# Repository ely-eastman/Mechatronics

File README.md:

# Mechatronics
For Northwestern's Advanced Mechatronics Class

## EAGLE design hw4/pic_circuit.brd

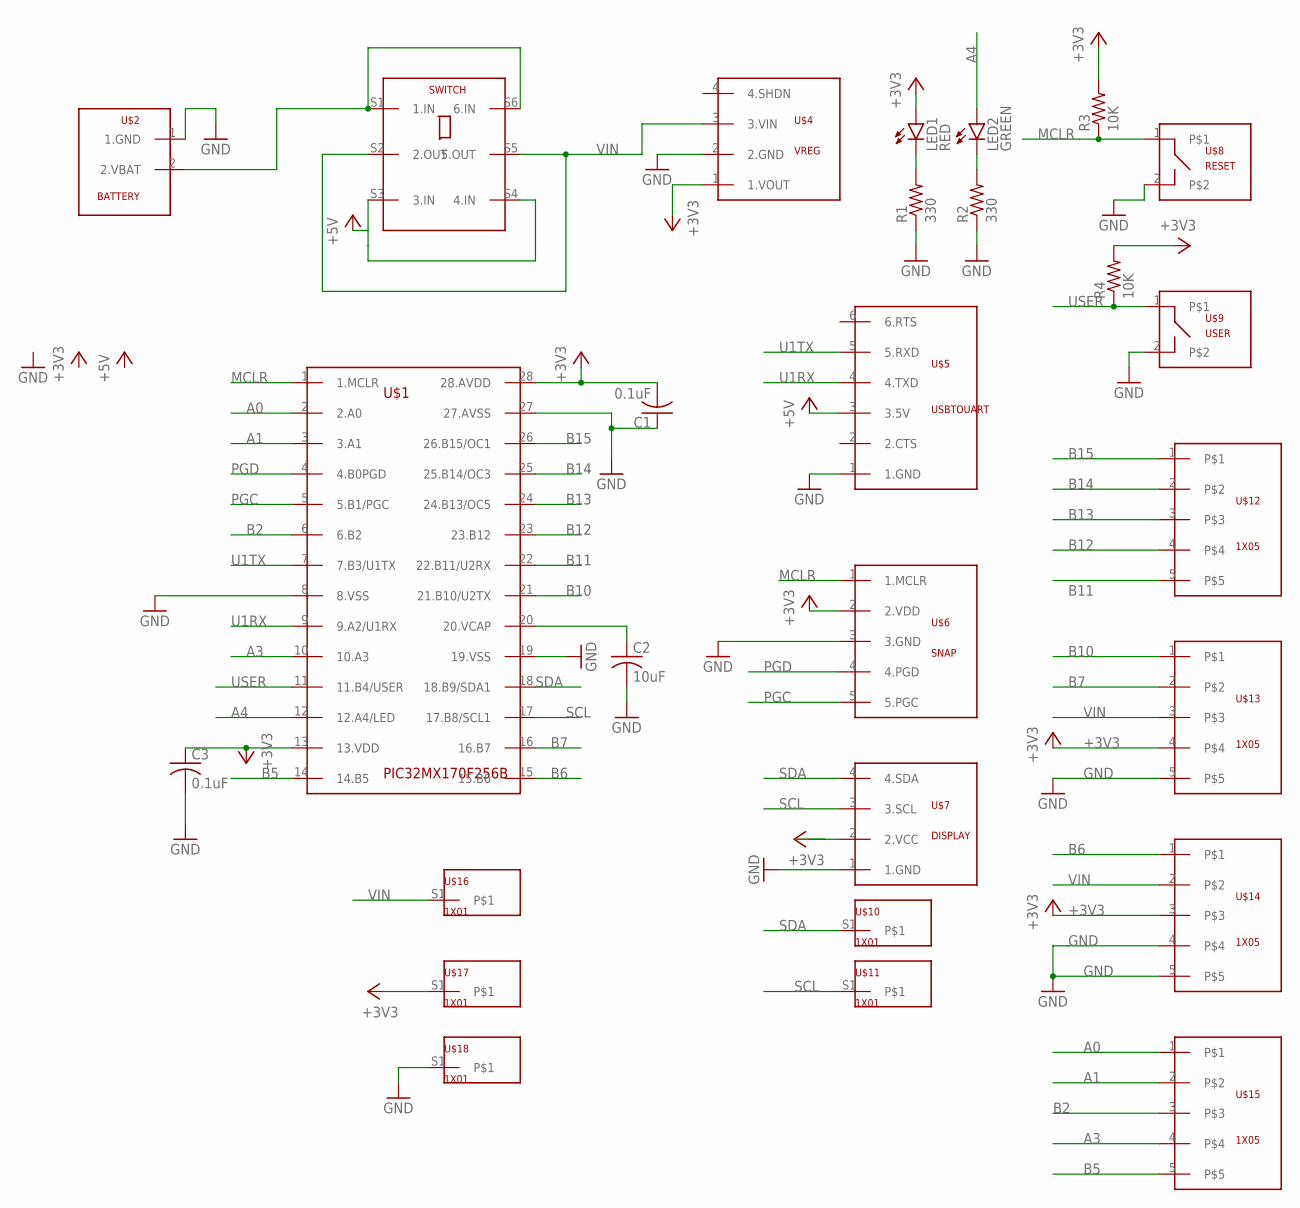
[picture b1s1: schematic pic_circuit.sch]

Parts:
C1, C3: 0.1uF; C025-024X044
C2: 10uF; C025-024X044
LED1: RED; LED3MM
LED2: GREEN; LED3MM
R1, R2: 330; 0207/7
R3, R4: 10K; 0207/7
SWITCH: SLIDE; SWITCH
U$1: PIC32MX170F256B; DIL28-3
U$2: BATTERY
U$4: VREG
U$5: USBTOUART; 1X06
U$6: SNAP
U$7: DISPLAY
U$8: RESET; BUTTON
U$9: USER; BUTTON
U$10, U$11, U$16, U$17, U$18: 1X01; 1X01_EE
U$12, U$13, U$14, U$15: 1X05; 1X05_EE

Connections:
+3V3: C1.2, C3.1, LED1.A, R3.2, R4.2, U$1.13 (13.VDD), U$1.28 (28.AVDD), U$4.1 (1.VOUT), U$6.2 (2.VDD), U$7.2 (2.VCC), U$13.4, U$14.3, U$17.S1
+5V: SWITCH.S3 (3.IN), SWITCH.S4 (4.IN), U$5.3 (3.5V)
A0: U$1.2 (2.A0), U$15.1
A1: U$1.3 (3.A1), U$15.2
A3: U$1.10 (10.A3), U$15.4
A4: LED2.A, U$1.12 (12.A4/LED)
B2: U$1.6 (6.B2), U$15.3
B5: U$1.14 (14.B5), U$15.5
B6: U$1.15 (15.B6), U$14.1
B7: U$1.16 (16.B7), U$13.2
B10: U$1.21 (21.B10/U2TX), U$13.1
B11: U$1.22 (22.B11/U2RX), U$12.5
B12: U$1.23 (23.B12), U$12.4
B13: U$1.24 (24.B13/OC5), U$12.3
B14: U$1.25 (25.B14/OC3), U$12.2
B15: U$1.26 (26.B15/OC1), U$12.1
GND: C1.1, C2.2, C3.2, R1.1, R2.1, U$1.8 (8.VSS), U$1.19 (19.VSS), U$1.27 (27.AVSS), U$2.1 (1.GND), U$4.2 (2.GND), U$5.1 (1.GND), U$6.3 (3.GND), U$7.1 (1.GND), U$8.2, U$9.2, U$13.5, U$14.4, U$14.5, U$18.S1
MCLR: R3.1, U$1.1 (1.MCLR), U$6.1 (1.MCLR), U$8.1
unnamed: LED1.K (C), R1.2
unnamed: SWITCH.S1 (1.IN), SWITCH.S6 (6.IN), U$2.2 (2.VBAT)
unnamed: C2.1, U$1.20 (20.VCAP)
unnamed: LED2.K (C), R2.2
PGC: U$1.5 (5.B1/PGC), U$6.5 (5.PGC)
PGD: U$1.4 (4.B0PGD), U$6.4 (4.PGD)
SCL: U$1.17 (17.B8/SCL1), U$7.3 (3.SCL), U$11.S1
SDA: U$1.18 (18.B9/SDA1), U$7.4 (4.SDA), U$10.S1
U1RX: U$1.9 (9.A2/U1RX), U$5.4 (4.TXD)
U1TX: U$1.7 (7.B3/U1TX), U$5.5 (5.RXD)
USER: R4.1, U$1.11 (11.B4/USER), U$9.1
VIN: SWITCH.S2 (2.OUT), SWITCH.S5 (5.OUT), U$4.3 (3.VIN), U$13.3, U$14.2, U$16.S1

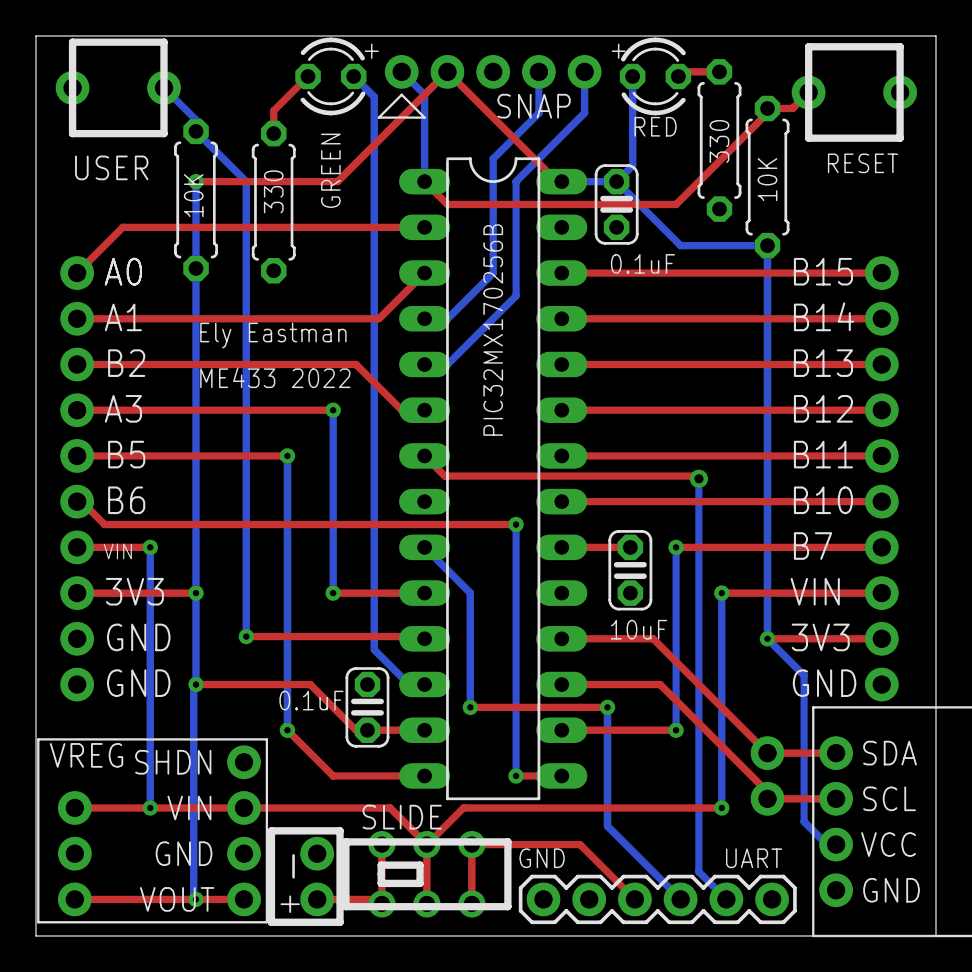
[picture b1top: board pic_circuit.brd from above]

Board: 2 copper layers, 50.0 x 50.0 mm, 27 parts (0 on the bottom side), 30 nets.

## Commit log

2022-03-31 Setting up mechatronics repo
2022-04-04 hw2 project file
    Added homework two project file for source code
2022-04-05 Create empty
2022-04-07 Homework 3
2022-04-13 PCB Files
